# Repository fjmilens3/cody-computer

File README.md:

# The Cody Computer Project

This repository contains the design files and source code for the Cody 
Computer, an 8-bit home computer built around the WDC 65C02 and the 
Parallax Propeller.

Each subdirectory contains a portion of the design:

- `KiCad` contains the design files for the Cody Computer's electronics.
- `OpenSCAD` contains the design files for the Cody Computer's printable parts.
- `PDF` contains generated PDFs of the KiCad schematics.
- `Spin` contains the Propeller `.spin` files for the Propeller's firmware.
- `STL` contains the generated STL files suitable for slicing and printing.
- `Tass` contains the `64tass` assembly files for Cody BASIC and demo programs.
- `CodyBASIC` contains some sample Cody BASIC programs used for demo purposes.
- `BillOfMaterials` contains spreadsheets with possible options for sourcing parts.

All design files and sources are released under the GPL version 3. A mention
of the Cody Computer in any derived works is also appreciated.

__The Cody Computer Book__ detailing the project is not released under the GPL
but may be freely distributed. Visit 
[www.codycomputer.org](https://www.codycomputer.org) for more information.

If any technical issues or inaccuracies are found in any of the material,
please reach out to the author or raise an issue on GitHub.

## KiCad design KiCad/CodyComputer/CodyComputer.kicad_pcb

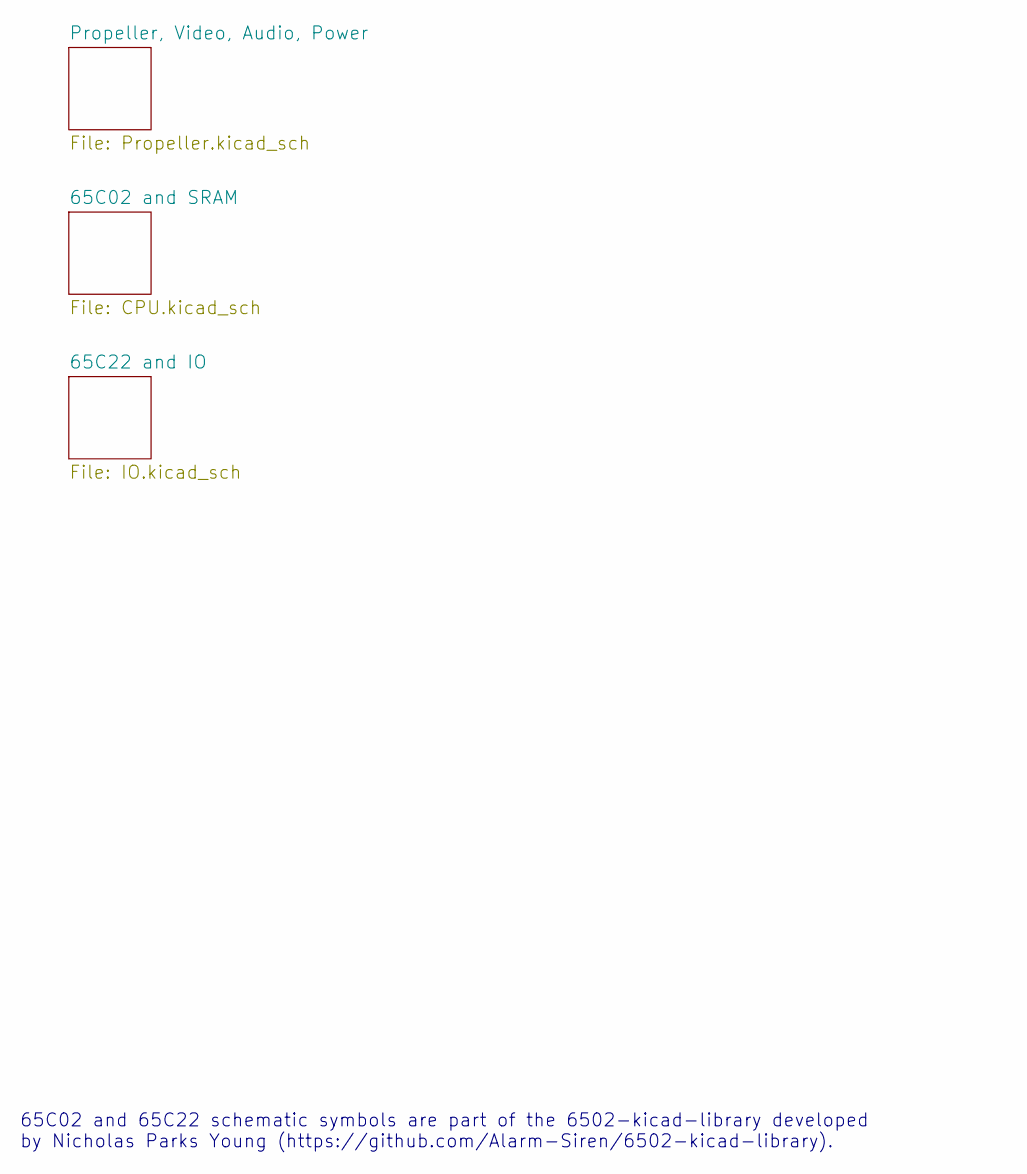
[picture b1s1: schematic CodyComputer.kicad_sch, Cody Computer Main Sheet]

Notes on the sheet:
65C02 and 65C22 schematic symbols are part of the 6502-kicad-library developed by Nicholas Parks Young (https://github.com/Alarm-Siren/6502-kicad-library).

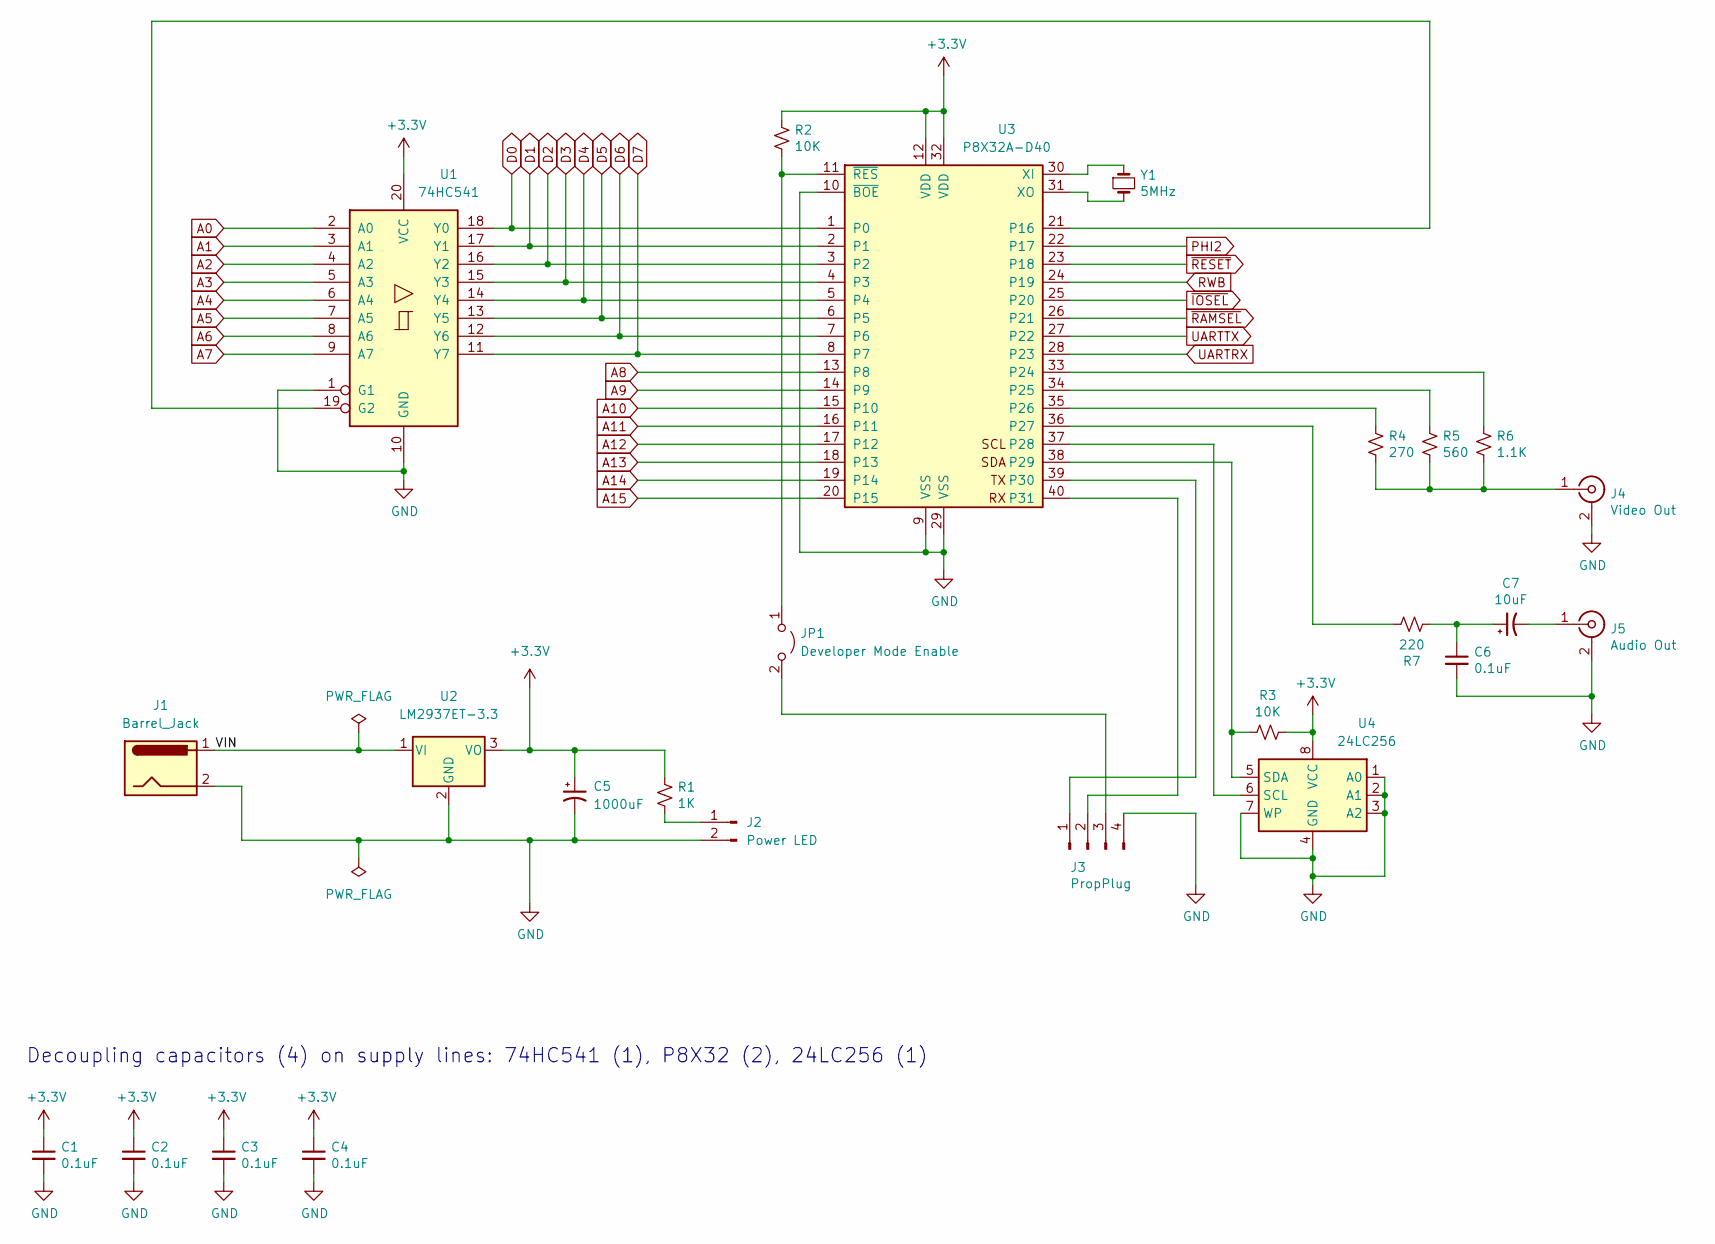
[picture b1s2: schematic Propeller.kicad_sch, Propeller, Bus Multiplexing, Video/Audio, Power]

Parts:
C1, C2, C3, C4, C6: 0.1uF; C_Disc_D3.8mm_W2.6mm_P2.50mm
C5: 1000uF; CP_Radial_D8.0mm_P3.50mm
C7: 10uF; CP_Radial_D5.0mm_P2.00mm
J1: Barrel_Jack; BarrelJack_Horizontal
J2: Power LED; PinHeader_1x02_P2.54mm_Vertical
J3: PropPlug; PinHeader_1x04_P2.54mm_Horizontal
J4: Video Out; CodyRCAJack
J5: Audio Out; CodyRCAJack
JP1: Developer Mode Enable; PinHeader_1x02_P2.54mm_Vertical
R1: 1K; R_Axial_DIN0207_L6.3mm_D2.5mm_P7.62mm_Horizontal
R2: 10K; R_Axial_DIN0207_L6.3mm_D2.5mm_P2.54mm_Vertical
R3: 10K; R_Axial_DIN0207_L6.3mm_D2.5mm_P7.62mm_Horizontal
R4: 270; R_Axial_DIN0207_L6.3mm_D2.5mm_P7.62mm_Horizontal
R5: 560; R_Axial_DIN0207_L6.3mm_D2.5mm_P7.62mm_Horizontal
R6: 1.1K; R_Axial_DIN0207_L6.3mm_D2.5mm_P7.62mm_Horizontal
R7: 220; R_Axial_DIN0207_L6.3mm_D2.5mm_P7.62mm_Horizontal
U1: 74HC541; DIP-20_W7.62mm_Socket
U2: LM2937ET-3.3; TO-220-3_Horizontal_TabDown
U3: P8X32A-D40; DIP-40_W15.24mm_Socket
U4: 24LC256; DIP-8_W7.62mm_Socket
Y1: 5MHz; Crystal_HC49-U_Vertical

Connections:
+3V3: C1.1, C2.1, C3.1, C4.1, C5.1, R1.2, R2.2, R3.2, U1.20 (VCC), U2.3 (VO), U3.12 (VDD), U3.32 (VDD), U4.8 (VCC); also elsewhere on the board
/Propeller, Video, Audio, Power/VIN: J1.1, U2.1 (VI); also elsewhere on the board
A0: U1.2 (A0); also elsewhere on the board
A1: U1.3 (A1); also elsewhere on the board
A2: U1.4 (A2); also elsewhere on the board
A3: U1.5 (A3); also elsewhere on the board
A4: U1.6 (A4); also elsewhere on the board
A5: U1.7 (A5); also elsewhere on the board
A6: U1.8 (A6); also elsewhere on the board
A7: U1.9 (A7); also elsewhere on the board
A8: U3.13 (P8); also elsewhere on the board
A9: U3.14 (P9); also elsewhere on the board
A10: U3.15 (P10); also elsewhere on the board
A11: U3.16 (P11); also elsewhere on the board
A12: U3.17 (P12); also elsewhere on the board
A13: U3.18 (P13); also elsewhere on the board
A14: U3.19 (P14); also elsewhere on the board
A15: U3.20 (P15); also elsewhere on the board
D0: U1.18 (Y0), U3.1 (P0); also elsewhere on the board
D1: U1.17 (Y1), U3.2 (P1); also elsewhere on the board
D2: U1.16 (Y2), U3.3 (P2); also elsewhere on the board
D3: U1.15 (Y3), U3.4 (P3); also elsewhere on the board
D4: U1.14 (Y4), U3.5 (P4); also elsewhere on the board
D5: U1.13 (Y5), U3.6 (P5); also elsewhere on the board
D6: U1.12 (Y6), U3.7 (P6); also elsewhere on the board
D7: U1.11 (Y7), U3.8 (P7); also elsewhere on the board
GND: C1.2, C2.2, C3.2, C4.2, C5.2, C6.2, J1.2, J2.2, J3.4, J4.2 (Ext), J5.2 (Ext), U1.1 (G1), U1.10 (GND), U2.2 (GND), U3.9 (VSS), U3.10 (~BOE), U3.29 (VSS), U4.1 (A0), U4.2 (A1), U4.3 (A2), U4.4 (GND), U4.7 (WP); also elsewhere on the board
unnamed: C6.1, C7.1, R7.1
unnamed: C7.2, J5.1 (In)
unnamed: J2.1, R1.1
unnamed: J3.1, U3.39 (P30)
unnamed: J3.2, U3.40 (P31)
unnamed: J3.3, JP1.2 (B)
unnamed: J4.1 (In), R4.1, R5.1, R6.1
unnamed: JP1.1 (A), R2.1, U3.11 (~RES)
unnamed: R3.1, U3.38 (P29), U4.5 (SDA)
unnamed: R4.2, U3.35 (P26)
unnamed: R5.2, U3.34 (P25)
unnamed: R6.2, U3.33 (P24)
unnamed: R7.2, U3.36 (P27)
unnamed: U1.19 (G2), U3.21 (P16)
unnamed: U3.30 (XI), Y1.1
unnamed: U3.31 (XO), Y1.2
unnamed: U3.37 (P28), U4.6 (SCL)
PHI2: U3.22 (P17); also elsewhere on the board
RWB: U3.24 (P19); also elsewhere on the board
UARTRX: U3.28 (P23); also elsewhere on the board
UARTTX: U3.27 (P22); also elsewhere on the board
~IOSEL: U3.25 (P20); also elsewhere on the board
~RAMSEL: U3.26 (P21); also elsewhere on the board
~RESET: U3.23 (P18); also elsewhere on the board

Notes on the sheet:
Decoupling capacitors (4) on supply lines: 74HC541 (1), P8X32 (2), 24LC256 (1)

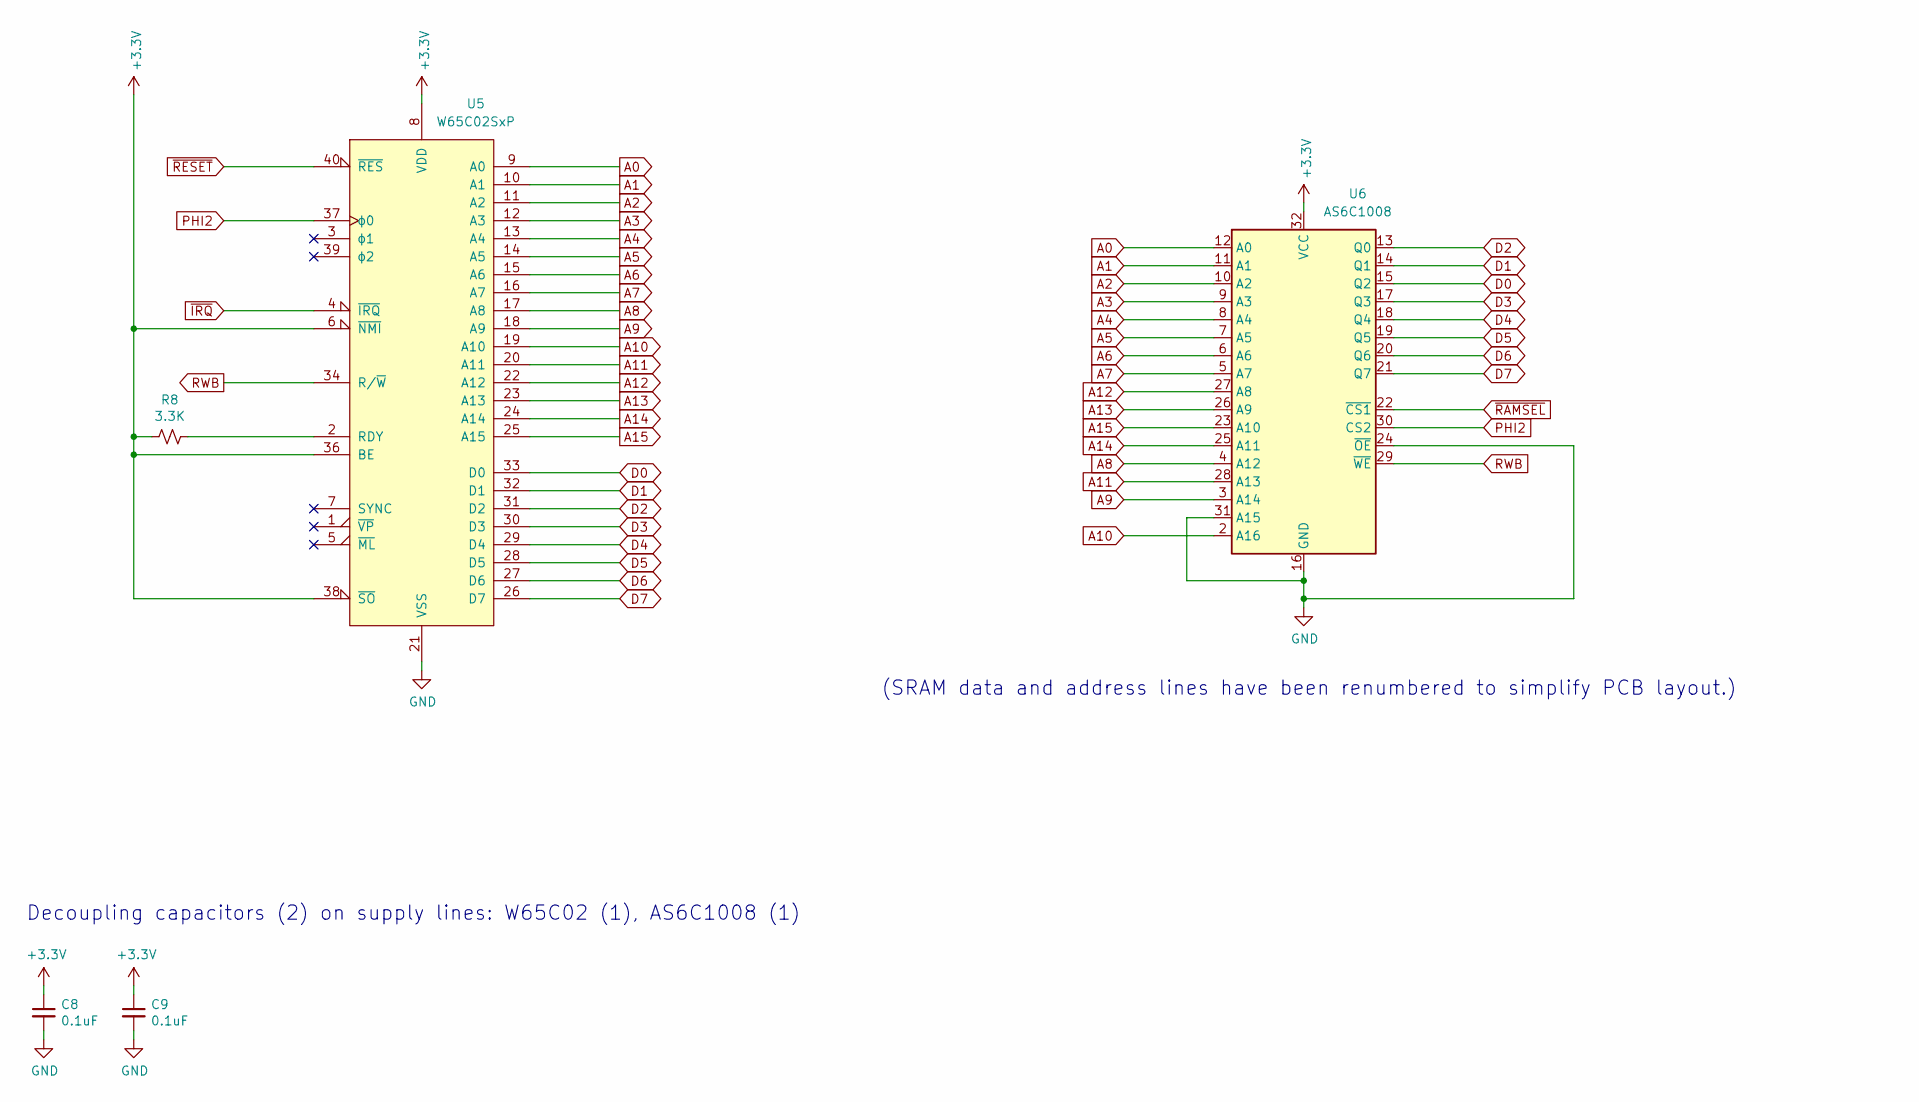
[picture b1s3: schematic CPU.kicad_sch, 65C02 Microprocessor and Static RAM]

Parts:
C8, C9: 0.1uF; C_Disc_D3.8mm_W2.6mm_P2.50mm
R8: 3.3K; R_Axial_DIN0207_L6.3mm_D2.5mm_P7.62mm_Horizontal
U5: W65C02SxP; DIP-40_W15.24mm_Socket
U6: AS6C1008; DIP-32_W15.24mm_Socket

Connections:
+3V3: C8.1, C9.1, R8.2, U5.6 (~NMI), U5.8 (VDD), U5.36 (BE), U5.38 (~SO), U6.32 (VCC); also elsewhere on the board
A0: U5.9 (A0), U6.12 (A0); also elsewhere on the board
A1: U5.10 (A1), U6.11 (A1); also elsewhere on the board
A2: U5.11 (A2), U6.10 (A2); also elsewhere on the board
A3: U5.12 (A3), U6.9 (A3); also elsewhere on the board
A4: U5.13 (A4), U6.8 (A4); also elsewhere on the board
A5: U5.14 (A5), U6.7 (A5); also elsewhere on the board
A6: U5.15 (A6), U6.6 (A6); also elsewhere on the board
A7: U5.16 (A7), U6.5 (A7); also elsewhere on the board
A8: U5.17 (A8), U6.4 (A12); also elsewhere on the board
A9: U5.18 (A9), U6.3 (A14); also elsewhere on the board
A10: U5.19 (A10), U6.2 (A16); also elsewhere on the board
A11: U5.20 (A11), U6.28 (A13); also elsewhere on the board
A12: U5.22 (A12), U6.27 (A8); also elsewhere on the board
A13: U5.23 (A13), U6.26 (A9); also elsewhere on the board
A14: U5.24 (A14), U6.25 (A11); also elsewhere on the board
A15: U5.25 (A15), U6.23 (A10); also elsewhere on the board
D0: U5.33 (D0), U6.15 (Q2); also elsewhere on the board
D1: U5.32 (D1), U6.14 (Q1); also elsewhere on the board
D2: U5.31 (D2), U6.13 (Q0); also elsewhere on the board
D3: U5.30 (D3), U6.17 (Q3); also elsewhere on the board
D4: U5.29 (D4), U6.18 (Q4); also elsewhere on the board
D5: U5.28 (D5), U6.19 (Q5); also elsewhere on the board
D6: U5.27 (D6), U6.20 (Q6); also elsewhere on the board
D7: U5.26 (D7), U6.21 (Q7); also elsewhere on the board
GND: C8.2, C9.2, U5.21 (VSS), U6.16 (GND), U6.24 (~OE), U6.31 (A15); also elsewhere on the board
unnamed: R8.1, U5.2 (RDY)
PHI2: U5.37 (ϕ0), U6.30 (CS2); also elsewhere on the board
RWB: U5.34 (R/~W), U6.29 (~WE); also elsewhere on the board
~IRQ: U5.4 (~IRQ); also elsewhere on the board
~RAMSEL: U6.22 (~CS1); also elsewhere on the board
~RESET: U5.40 (~RES); also elsewhere on the board

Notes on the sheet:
(SRAM data and address lines have been renumbered to simplify PCB layout.)
Decoupling capacitors (2) on supply lines: W65C02 (1), AS6C1008 (1)

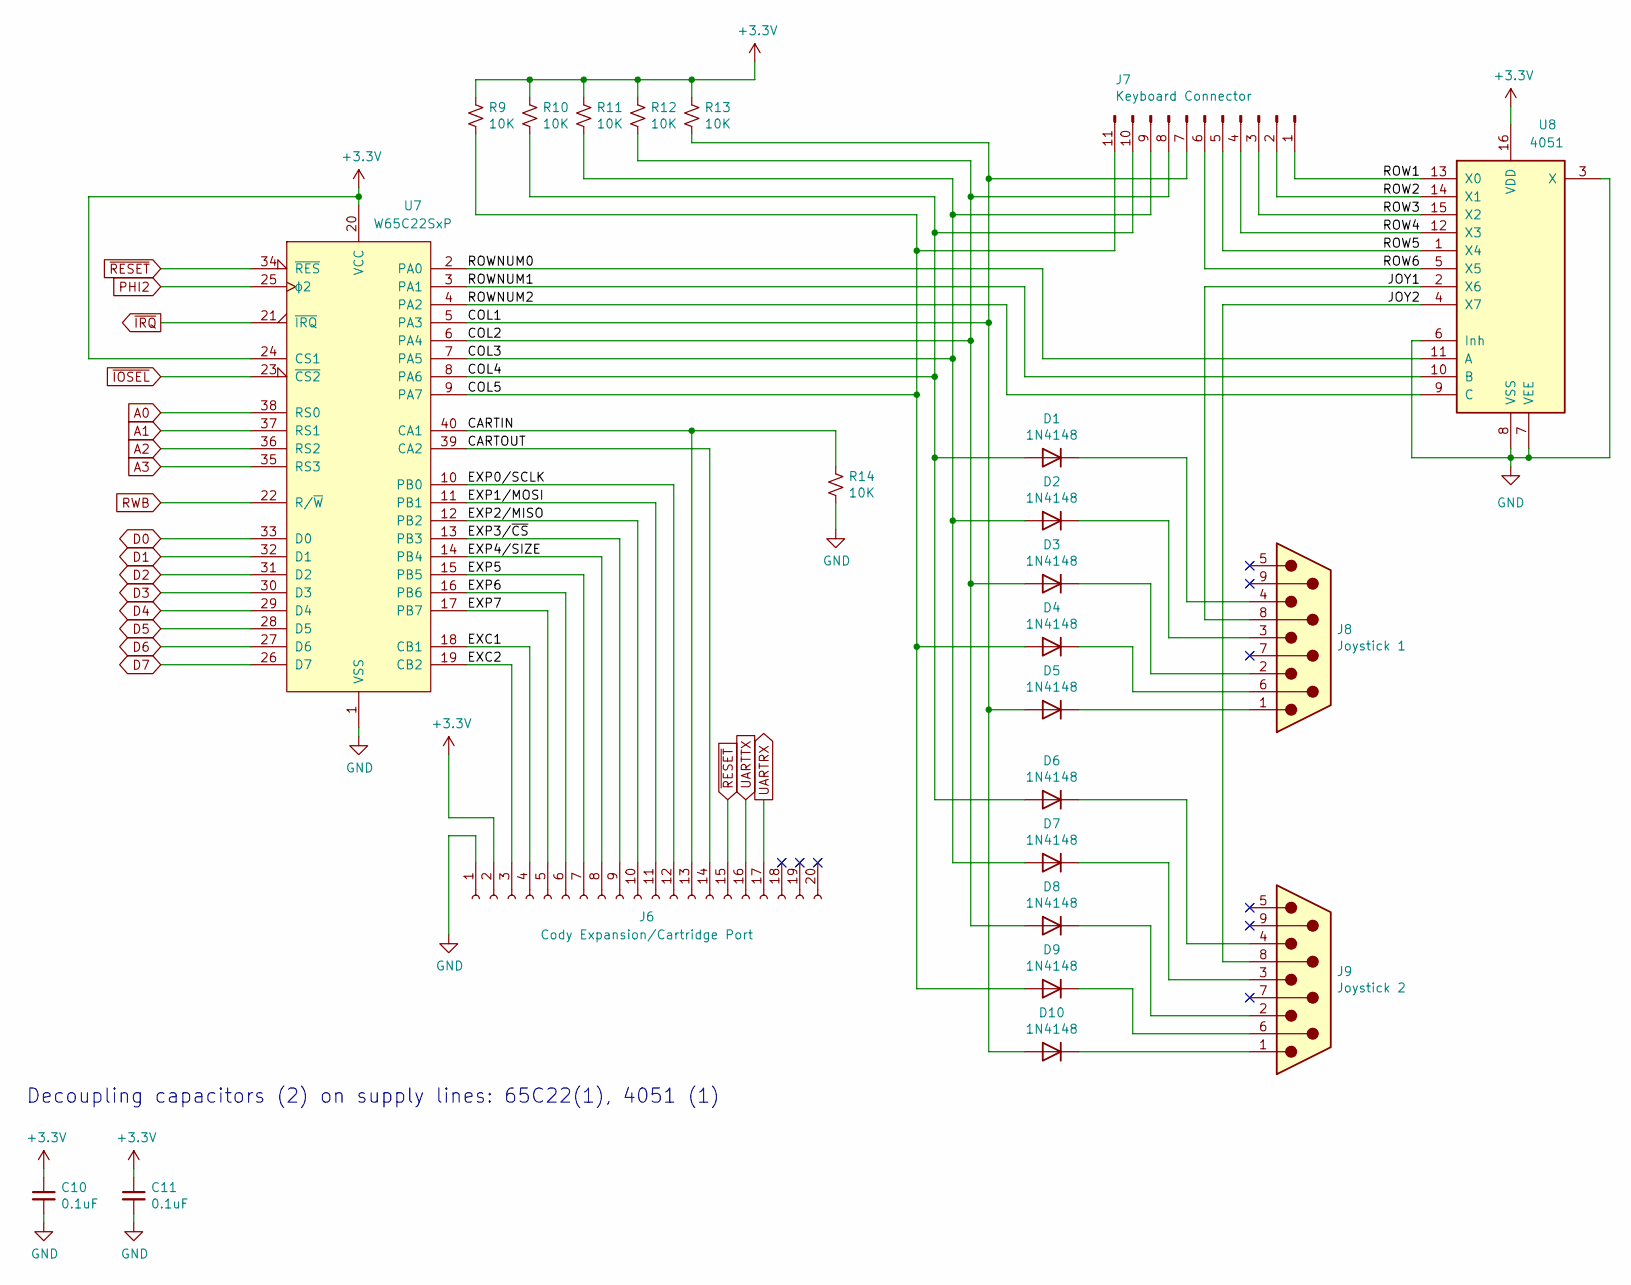
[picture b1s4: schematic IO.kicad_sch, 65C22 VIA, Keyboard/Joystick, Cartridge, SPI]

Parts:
C10, C11: 0.1uF; C_Disc_D3.8mm_W2.6mm_P2.50mm
D1, D2, D3, D4, D5, D6, D7, D8, D9, D10: 1N4148; D_DO-34_SOD68_P7.62mm_Horizontal
J6: Cody Expansion/Cartridge Port; PinSocket_1x20_P2.54mm_Horizontal
J7: Keyboard Connector; PinHeader_1x11_P2.54mm_Vertical
J8: Joystick 1; DSUB-9_Male_Horizontal_P2.77x2.84mm_EdgePinOffset7.70mm_Hou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
J9: Joystick 2; DSUB-9_Male_Horizontal_P2.77x2.84mm_EdgePinOffset7.70mm_Hou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
R9, R10, R11, R12, R13: 10K; R_Axial_DIN0207_L6.3mm_D2.5mm_P7.62mm_Horizontal
R14: 10K; R_Axial_DIN0207_L6.3mm_D2.5mm_P2.54mm_Vertical
U7: W65C22SxP; DIP-40_W15.24mm_Socket
U8: 4051; DIP-16_W7.62mm_Socket

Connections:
+3V3: C10.1, C11.1, J6.2, R9.2, R10.2, R11.2, R12.2, R13.2, U7.20 (VCC), U7.24 (CS1), U8.16 (VDD); also elsewhere on the board
/65C22 and IO/CARTIN: J6.13, R14.2, U7.40 (CA1)
/65C22 and IO/CARTOUT: J6.14, U7.39 (CA2)
/65C22 and IO/COL1: D5.2 (A), D10.2 (A), J7.7, R13.1, U7.5 (PA3)
/65C22 and IO/COL2: D3.2 (A), D8.2 (A), J7.8, R12.1, U7.6 (PA4)
/65C22 and IO/COL3: D2.2 (A), D7.2 (A), J7.9, R11.1, U7.7 (PA5)
/65C22 and IO/COL4: D1.2 (A), D6.2 (A), J7.10, R10.1, U7.8 (PA6)
/65C22 and IO/COL5: D4.2 (A), D9.2 (A), J7.11, R9.1, U7.9 (PA7)
/65C22 and IO/EXC1: J6.4, U7.18 (CB1)
/65C22 and IO/EXC2: J6.3, U7.19 (CB2)
/65C22 and IO/EXP0/SCLK: J6.12, U7.10 (PB0)
/65C22 and IO/EXP1/MOSI: J6.11, U7.11 (PB1)
/65C22 and IO/EXP2/MISO: J6.10, U7.12 (PB2)
/65C22 and IO/EXP3/~CS: J6.9, U7.13 (PB3)
/65C22 and IO/EXP4/SIZE: J6.8, U7.14 (PB4)
/65C22 and IO/EXP5: J6.7, U7.15 (PB5)
/65C22 and IO/EXP6: J6.6, U7.16 (PB6)
/65C22 and IO/EXP7: J6.5, U7.17 (PB7)
/65C22 and IO/JOY1: J8.8, U8.2 (X6)
/65C22 and IO/JOY2: J9.8, U8.4 (X7)
/65C22 and IO/ROW1: J7.1, U8.13 (X0)
/65C22 and IO/ROW2: J7.2, U8.14 (X1)
/65C22 and IO/ROW3: J7.3, U8.15 (X2)
/65C22 and IO/ROW4: J7.4, U8.12 (X3)
/65C22 and IO/ROW5: J7.5, U8.1 (X4)
/65C22 and IO/ROW6: J7.6, U8.5 (X5)
/65C22 and IO/ROWNUM0: U7.2 (PA0), U8.11 (A)
/65C22 and IO/ROWNUM1: U7.3 (PA1), U8.10 (B)
/65C22 and IO/ROWNUM2: U7.4 (PA2), U8.9 (C)
A0: U7.38 (RS0); also elsewhere on the board
A1: U7.37 (RS1); also elsewhere on the board
A2: U7.36 (RS2); also elsewhere on the board
A3: U7.35 (RS3); also elsewhere on the board
D0: U7.33 (D0); also elsewhere on the board
D1: U7.32 (D1); also elsewhere on the board
D2: U7.31 (D2); also elsewhere on the board
D3: U7.30 (D3); also elsewhere on the board
D4: U7.29 (D4); also elsewhere on the board
D5: U7.28 (D5); also elsewhere on the board
D6: U7.27 (D6); also elsewhere on the board
D7: U7.26 (D7); also elsewhere on the board
GND: C10.2, C11.2, J6.1, R14.1, U7.1 (VSS), U8.3 (X), U8.6 (Inh), U8.7 (VEE), U8.8 (VSS); also elsewhere on the board
unnamed: D1.1 (K), J8.4
unnamed: D2.1 (K), J8.3
unnamed: D3.1 (K), J8.2
unnamed: D4.1 (K), J8.6
unnamed: D5.1 (K), J8.1
unnamed: D6.1 (K), J9.4
unnamed: D7.1 (K), J9.3
unnamed: D8.1 (K), J9.2
unnamed: D9.1 (K), J9.6
unnamed: D10.1 (K), J9.1
PHI2: U7.25 (ϕ2); also elsewhere on the board
RWB: U7.22 (R/~W); also elsewhere on the board
UARTRX: J6.17; also elsewhere on the board
UARTTX: J6.16; also elsewhere on the board
~IOSEL: U7.23 (~CS2); also elsewhere on the board
~IRQ: U7.21 (~IRQ); also elsewhere on the board
~RESET: J6.15, U7.34 (~RES); also elsewhere on the board

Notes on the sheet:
Decoupling capacitors (2) on supply lines: 65C22(1), 4051 (1)

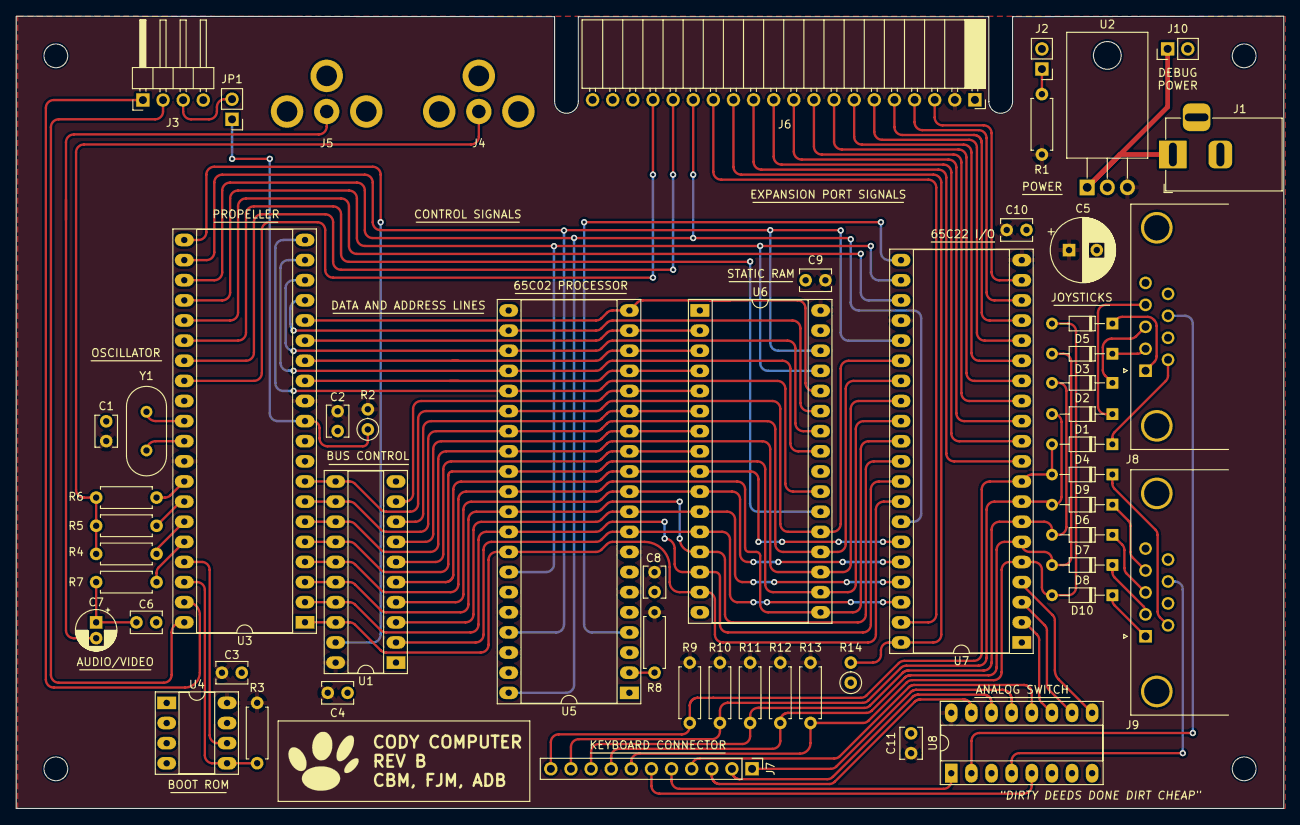
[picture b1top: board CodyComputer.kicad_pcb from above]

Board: 2 copper layers, 160.0 x 100.0 mm, 55 parts (0 on the bottom side), 91 nets.

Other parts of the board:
J10: Debug Power (Do Not Populate); PinHeader_1x02_P2.54mm_Vertical

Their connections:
/Propeller, Video, Audio, Power/VIN: J10.1; also elsewhere on the board
GND: J10.2; also elsewhere on the board

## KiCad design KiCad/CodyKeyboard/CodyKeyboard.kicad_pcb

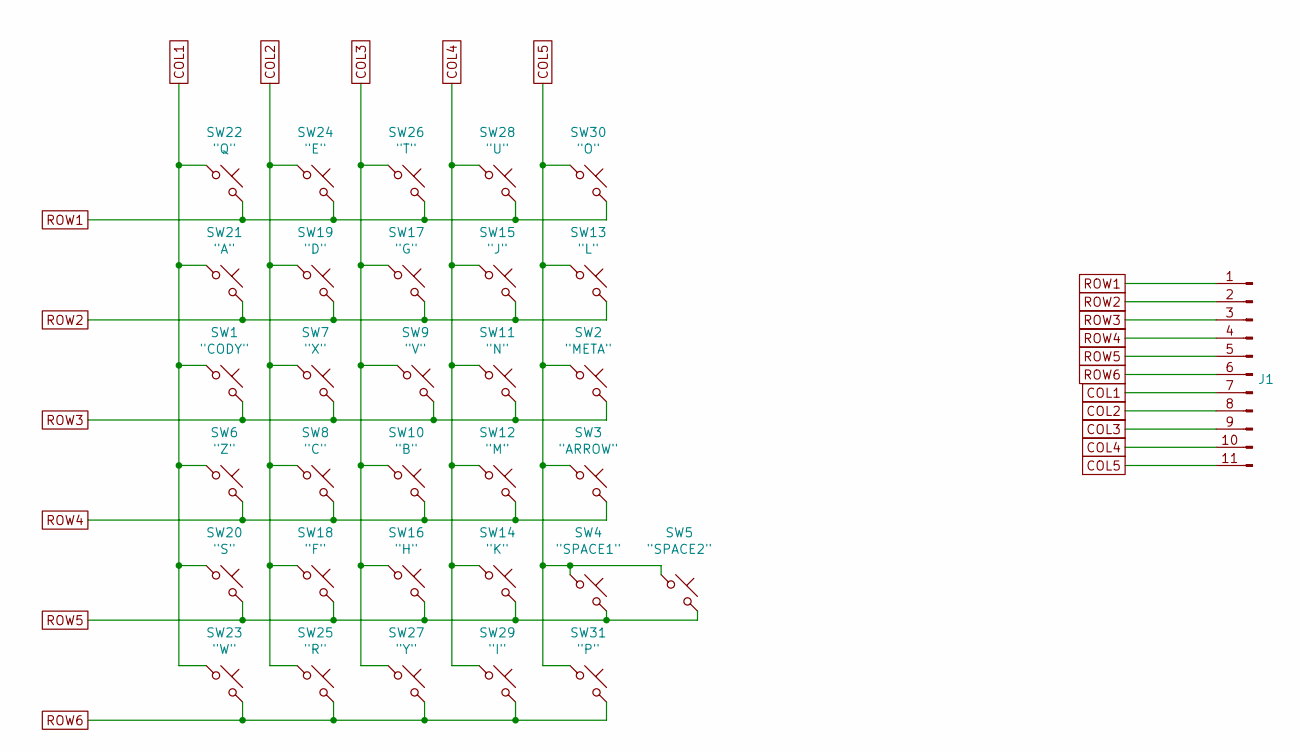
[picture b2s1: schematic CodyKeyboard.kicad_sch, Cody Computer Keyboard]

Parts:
J1: PinHeader_1x11_P2.54mm_Horizontal
SW1: "CODY"; CodyKeyboardSwitch
SW2: "META"; CodyKeyboardSwitch
SW3: "ARROW"; CodyKeyboardSwitch
SW4: "SPACE1"; CodyKeyboardSwitch
SW5: "SPACE2"; CodyKeyboardSwitch
SW6: "Z"; CodyKeyboardSwitch
SW7: "X"; CodyKeyboardSwitch
SW8: "C"; CodyKeyboardSwitch
SW9: "V"; CodyKeyboardSwitch
SW10: "B"; CodyKeyboardSwitch
SW11: "N"; CodyKeyboardSwitch
SW12: "M"; CodyKeyboardSwitch
SW13: "L"; CodyKeyboardSwitch
SW14: "K"; CodyKeyboardSwitch
SW15: "J"; CodyKeyboardSwitch
SW16: "H"; CodyKeyboardSwitch
SW17: "G"; CodyKeyboardSwitch
SW18: "F"; CodyKeyboardSwitch
SW19: "D"; CodyKeyboardSwitch
SW20: "S"; CodyKeyboardSwitch
SW21: "A"; CodyKeyboardSwitch
SW22: "Q"; CodyKeyboardSwitch
SW23: "W"; CodyKeyboardSwitch
SW24: "E"; CodyKeyboardSwitch
SW25: "R"; CodyKeyboardSwitch
SW26: "T"; CodyKeyboardSwitch
SW27: "Y"; CodyKeyboardSwitch
SW28: "U"; CodyKeyboardSwitch
SW29: "I"; CodyKeyboardSwitch
SW30: "O"; CodyKeyboardSwitch
SW31: "P"; CodyKeyboardSwitch

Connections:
COL1: J1.7, SW1.1, SW6.1, SW20.1, SW21.1, SW22.1, SW23.1
COL2: J1.8, SW7.1, SW8.1, SW18.1, SW19.1, SW24.1, SW25.1
COL3: J1.9, SW9.1, SW10.1, SW16.1, SW17.1, SW26.1, SW27.1
COL4: J1.10, SW11.1, SW12.1, SW14.1, SW15.1, SW28.1, SW29.1
COL5: J1.11, SW2.1, SW3.1, SW4.1, SW5.1, SW13.1, SW30.1, SW31.1
ROW1: J1.1, SW22.2, SW24.2, SW26.2, SW28.2, SW30.2
ROW2: J1.2, SW13.2, SW15.2, SW17.2, SW19.2, SW21.2
ROW3: J1.3, SW1.2, SW2.2, SW7.2, SW9.2, SW11.2
ROW4: J1.4, SW3.2, SW6.2, SW8.2, SW10.2, SW12.2
ROW5: J1.5, SW4.2, SW5.2, SW14.2, SW16.2, SW18.2, SW20.2
ROW6: J1.6, SW23.2, SW25.2, SW27.2, SW29.2, SW31.2

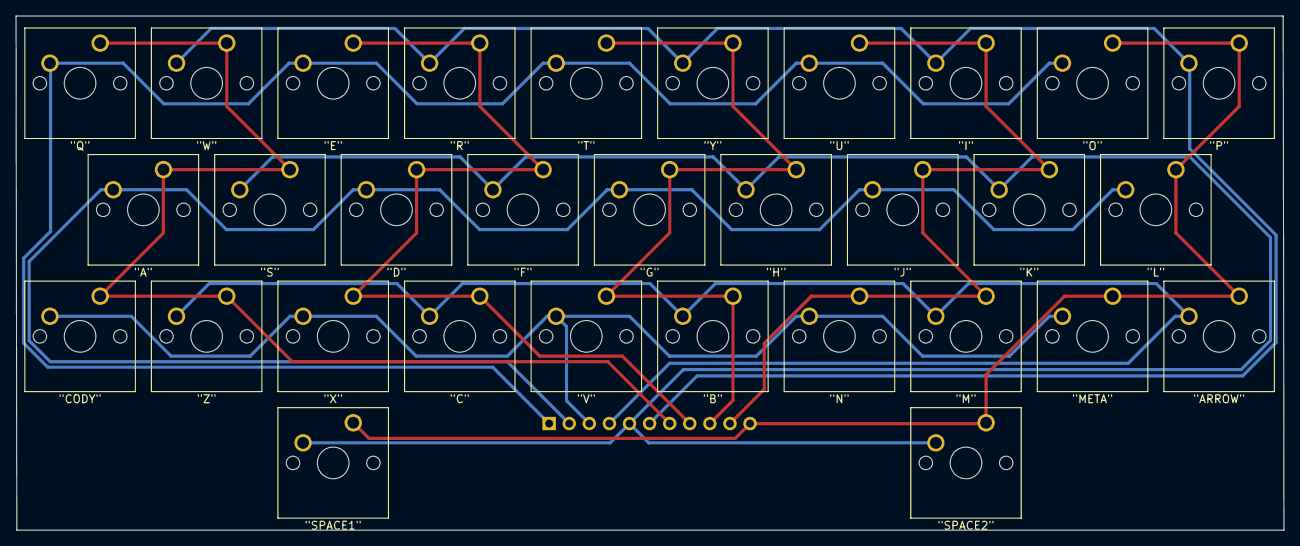
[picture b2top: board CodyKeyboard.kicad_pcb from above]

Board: 2 copper layers, 160.3 x 65.0 mm, 32 parts (1 on the bottom side), 11 nets.

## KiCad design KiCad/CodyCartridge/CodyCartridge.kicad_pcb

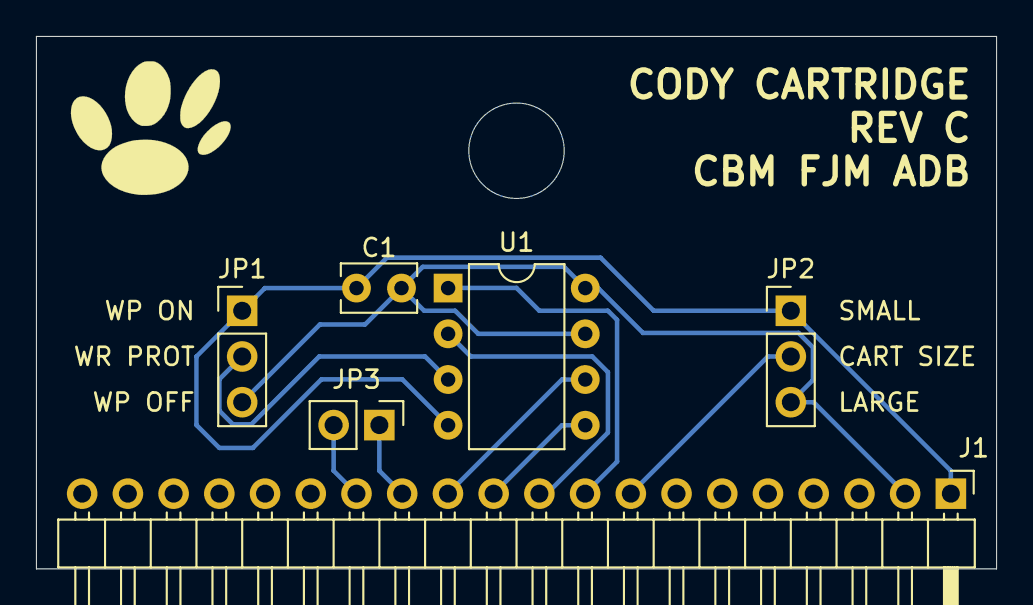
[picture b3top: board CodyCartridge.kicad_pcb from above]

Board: 2 copper layers, 53.3 x 29.6 mm, 6 parts (0 on the bottom side), 10 nets.

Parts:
C1: 0.1μF; C_Rect_L4.0mm_W2.5mm_P2.50mm
J1: Cody Expansion Port; PinHeader_1x20_P2.54mm_Horizontal
JP1: Cartridge Write-Protect; PinHeader_1x03_P2.54mm_Vertical
JP2: Cartridge Size; PinHeader_1x03_P2.54mm_Vertical
JP3: Cartridge Detect; PinHeader_1x02_P2.54mm_Vertical
U1: 25LCxxx; DIP-8_W7.62mm

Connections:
unnamed: C1.1, J1.2, JP1.3 (B), JP2.3 (B), U1.7 (~HOLD), U1.8 (VCC)
unnamed: C1.2, J1.1, JP1.1 (A), JP2.1 (A), U1.4 (GND)
unnamed: J1.8, JP2.2 (C)
unnamed: J1.9, U1.1 (~CS)
unnamed: J1.10, U1.2 (MISO)
unnamed: J1.11, U1.5 (MOSI)
unnamed: J1.12, U1.6 (SCK)
unnamed: J1.13, JP3.1 (A)
unnamed: J1.14, JP3.2 (B)
unnamed: JP1.2 (C), U1.3 (~WP)

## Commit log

2024-12-13 Add .gitignore file
2024-12-13 Copy KiCad projects into repository
2024-12-14 Add OpenSCAD files and supporting SVG files.
2024-12-14 Add STL files generated from OpenSCAD
2024-12-17 Add correct license headers before release.
2024-12-21 Add Propeller .spin files for firmware
2024-12-21 Add 64tass assembly files for Cody BASIC and demos
2024-12-21 Add demo programs in Cody BASIC
2024-12-24 Add exported PDF schematics
2024-12-24 Update README before release
2024-12-24 License header cleanup
2024-12-26 Add Propeller firmware and assembly example for bitmap mode
2024-12-26 Fix for resetting interrupts on warm reset
2025-01-07 Change socket footprints to long pads
2025-01-07 Fix DRC errors for long pads
2025-01-07 Update board revision to Rev B
2025-01-07 Move RCA connectors 1.7mm for punchout alignment
2025-01-07 Add debug power connector to schematic
2025-01-07 Add debug power connector to PCB
2025-01-07 Regenerate schematic PDF
2025-01-10 Move RCA connectors by additional 0.4mm
2025-01-10 Update date and time for PCB layout
2025-01-20 Keyboard-over-serial hack for early Witulski build
2025-02-07 Add electronics BOM with Mouser part numbers
2025-02-26 Fix typo in codytrek.bas
2025-02-26 Fix typo in codytrek.bas (#4)
2025-03-14 Extract INIT routine from MAIN
2025-03-14 Call INIT instead of MAIN when returning
2025-03-14 Update copyright
2025-03-14 Update Cody BASIC ROM
2025-03-14 Add example memory-resident program
2025-03-16 Refactor initialization and binary program load to avoid cartridge loops (#6)
2025-03-17 Free up space by page-aligning string tables
2025-03-17 Regenerate Cody BASIC ROM
2025-03-17 Free up ROM space by page-aligning string tables (#8)
2025-03-17 Make PROGEND modifiable as a zero-page variable
2025-03-17 Update resident code example to adjust program memory bounds
2025-03-17 Make the upper bound of BASIC program memory configurable (#10)
2025-03-18 Terminate string table entries using the high bit
2025-03-18 Rebuild Cody BASIC ROM
2025-03-18 Change configuration to two colors, 8 pixels
2025-03-18 Display repeating 'A' pattern for testing
2025-03-18 Free up additional space by using high bit to terminate string table entries (#12)
2025-03-25 Refactor render_chars for lowres mode
2025-03-25 Initial attempt at hires generation
2025-03-25 Update documentation with bitmap mode flag
2025-03-25 Call scanline renderer based on lores/hires mode
2025-03-25 Fix argument to REV instruction
2025-03-25 Add initial implementation of hires NTSC output
2025-03-25 Fix bug
2025-03-25 Minimal working hires assembly example
2025-03-25 Add screen and color data to example
2025-03-25 Remove dead code
2025-03-25 Use the Propeller's four-color output mode
2025-03-25 Fix documentation
2025-03-25 Rename example file
2025-03-25 Fix typo
2025-03-25 Add example for high-res bitmap mode
2025-03-25 Fix comment
2025-03-25 Comment fix
2025-03-27 Add high-resolution graphics and example code (#14)
2025-03-30 Fix typos in comments
2025-03-31 Optimize writes of high-res pixel and color data
2025-03-31 Simplify communications between video and scanline cogs
2025-03-31 Ignore vertical scrolling in high-res mode
2025-03-31 Fix the actual bug (pixel pattern mutation)
2025-03-31 Fix video corruption when switching back from hires to lores (#17)
2025-04-01 Change apply_row_effects to remember last position
2025-04-01 Fix looping
2025-04-02 Optimize fetching of row effects (#19)
2025-04-11 Correct number of DB9 connectors (2 per build)
2025-04-11 Add Makefile for building and uploading the Spin code
2025-04-11 Add missing proploader flag to actually program the EEPROM
    Without -e, it just loads the new firmware into RAM and it will be lost
    after a power cycle.
2025-04-12 Add comments
2025-04-13 Add new tokenizer variable to avoid clobbering SYS_A
2025-04-16 Add reset flag to proploader call
    This makes the Cody Computer automatically boot after the firmware is
    uploaded (default behavior is to leave the Propeller powered off,
    apparently) and for some reason also fixes the "EEPROM verify failed"
    errors I get at the end of the upload.
2025-04-16 Add convenience variable for specifying serial port for upload
2025-04-16 Add new tokenizer variable to avoid clobbering SYS_A (#22)
2025-04-16 Fix AB bug related to wraparound
2025-04-16 Move (commented debugging) PUTHEX routine
2025-04-17 Fix REM optimization bug (also fixes caps)
2025-04-17 Add Makefile for building and uploading the Spin code (#20)
2025-04-17 Cody BASIC tokenizer fixes for AA/AB and REM (#26)
2025-05-06 Add flag to turn off color video output
2025-05-12 Fix 'skip' at right side of scroll
2025-05-24 Fix 'skip' at right side of scroll (#29)
2025-05-25 Add video control register flag to turn off color video output (#28)
